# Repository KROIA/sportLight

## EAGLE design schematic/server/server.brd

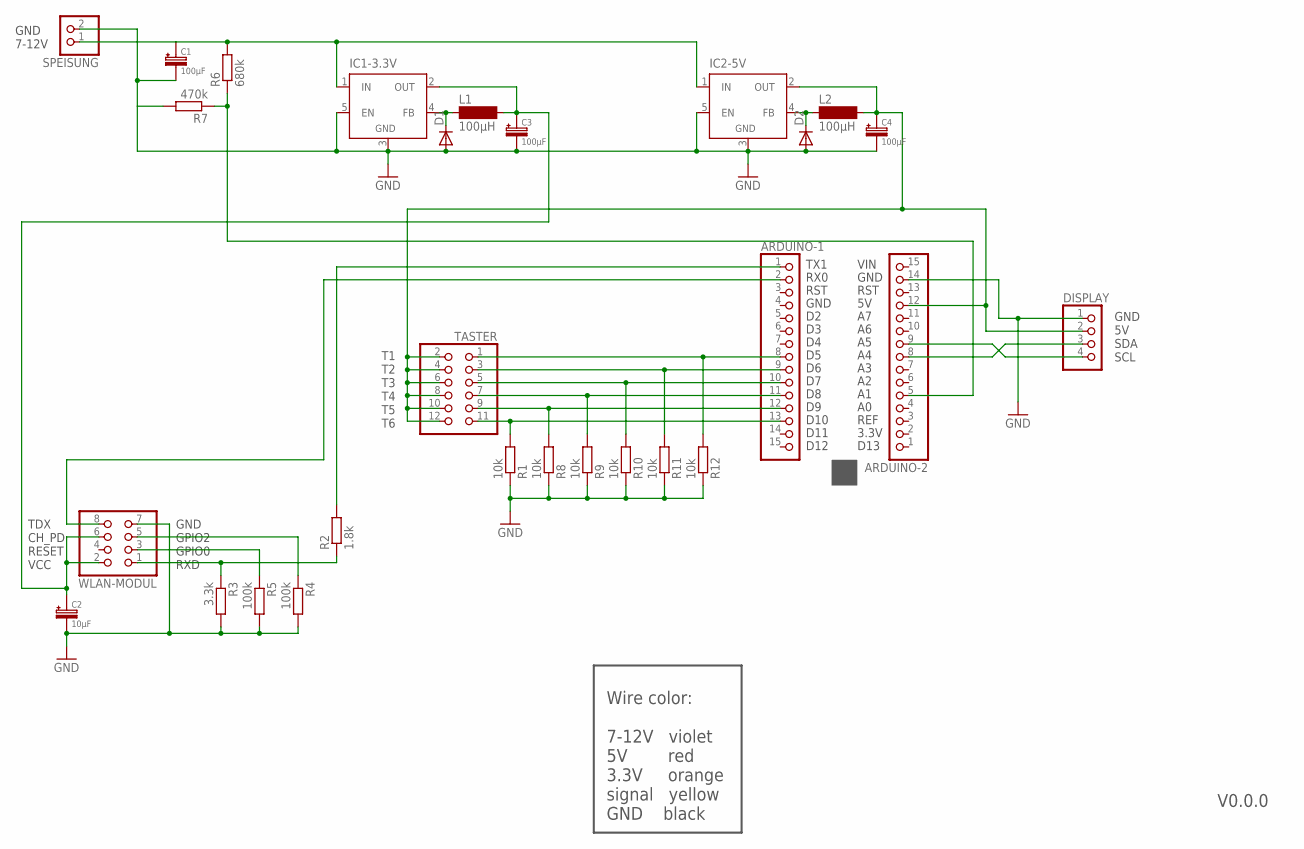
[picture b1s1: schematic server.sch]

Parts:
ARDUINO-1, ARDUINO-2: PINHD-1X15; 1X15
C1, C3, C4: 100µF; KONDENSATOR_ELEKTROLYT
C2: 10µF; KONDENSATOR_ELEKTROLYT
D1, D2: DIODE-D-2.5; D-2.5
DISPLAY: PINHD-1X4; 1X04
IC1-3.3V, IC2-5V: LM2596TV; TO220-51
L1, L2: 100µH; SM-L15A
R1: 10k; 0207/15
R2: 1.8k; 0207/10
R3: 3.3k; 0207/10
R4, R5: 100k; 0207/10
R6: 680k; 0204V
R7: 470k; 0204V
R8: 10k; 0207/12
R9: 10k; 0207/10
R10: 10k; 0207/7
R11: 10k; 0207/5V
R12: 10k; 0207/2V
SPEISUNG: PINHD-1X2; 1X02
TASTER: PINHD-2X6; 2X06
WLAN-MODUL: PINHD-2X4; 2X04

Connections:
GND: ARDUINO-2.14, C1.P$1, C2.P$1, C3.P$1, C4.P$1, D1.A, D2.A, DISPLAY.1, IC1-3.3V.3 (GND), IC1-3.3V.5 (EN), IC2-5V.3 (GND), IC2-5V.5 (EN), R1.1, R3.2, R4.2, R5.2, R7.2, R8.1, R9.1, R10.1, R11.1, R12.1, SPEISUNG.2, WLAN-MODUL.7
unnamed: D1.C, IC1-3.3V.4 (FB), L1.1
unnamed: ARDUINO-1.9, R11.2, TASTER.3
unnamed: C1.P$2, IC1-3.3V.1 (IN), IC2-5V.1 (IN), R6.2, SPEISUNG.1
unnamed: C2.P$2, C3.P$2, IC1-3.3V.2 (OUT), L1.2, WLAN-MODUL.2, WLAN-MODUL.6
unnamed: D2.C, IC2-5V.4 (FB), L2.1
unnamed: ARDUINO-1.13, R1.2, TASTER.11
unnamed: ARDUINO-2.5, R6.1, R7.1
unnamed: ARDUINO-2.8, DISPLAY.3
unnamed: ARDUINO-1.12, R8.2, TASTER.9
unnamed: ARDUINO-2.9, DISPLAY.4
unnamed: R2.1, R3.1, WLAN-MODUL.1
unnamed: R5.1, WLAN-MODUL.3
unnamed: R4.1, WLAN-MODUL.5
unnamed: ARDUINO-1.1, R2.2
unnamed: ARDUINO-1.2, WLAN-MODUL.8
unnamed: ARDUINO-1.11, R9.2, TASTER.7
unnamed: ARDUINO-1.10, R10.2, TASTER.5
unnamed: ARDUINO-2.12, C4.P$2, DISPLAY.2, IC2-5V.2 (OUT), L2.2, TASTER.2, TASTER.4, TASTER.6, TASTER.8, TASTER.10, TASTER.12
unnamed: ARDUINO-1.8, R12.2, TASTER.1

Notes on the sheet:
TX1 RX0 RST GND D2 D3 D4 D5 D6 D7 D8 D9 D10 D11 D12
GND GPIO2 GPIO0 RXD
TDX CH_PD RESET VCC
GND 7-12V
GND 5V SDA SCL
VIN GND RST 5V A7 A6 A5 A4 A3 A2 A1 A0 REF 3.3V D13
V0.0.0
T1 T2 T3 T4 T5 T6
Wire color: 7-12V violet 5V red 3.3V orange signal yellow GND black

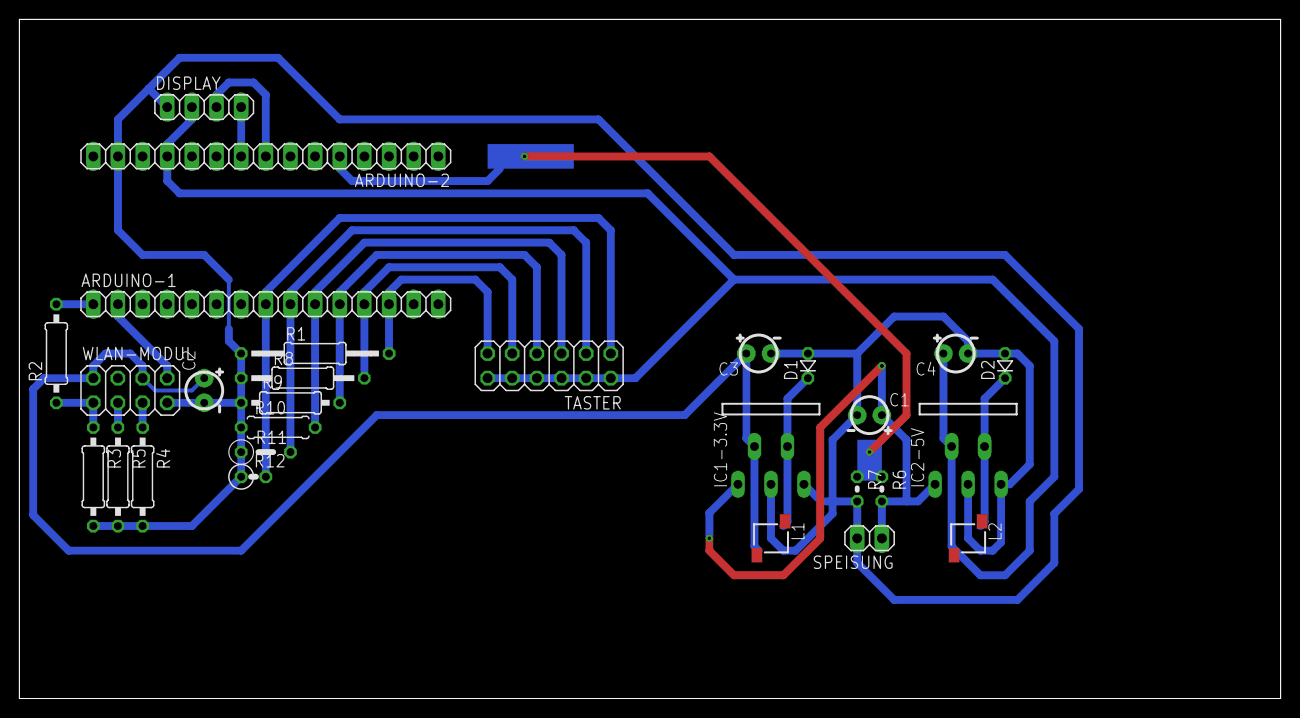
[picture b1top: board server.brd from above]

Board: 2 copper layers, 130.0 x 70.0 mm, 28 parts (0 on the bottom side), 20 nets.

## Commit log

2018-06-20 + sportlight
2018-06-26 v0.2.0
    Adding:
    voltage sensor
    MPU6050 calibrate
2018-06-28 + RGB_mode
2018-06-28 + serialCommand
    data|voltage|time
2018-06-28 voltageDisplayAnimationChange
2018-06-29 + server schematic
2018-06-29 + commands
2018-07-06 + server board
2018-07-10 pinoutChange
2018-07-11 + voltageDisplay
2018-07-11 + Mode
    + Menue_Info
    + Menue_Modus
2018-07-14 + mqtt
2018-07-19 bugfix
2018-08-14 +
    + Box[x] voltage in menue/info
    + testmodie
2018-09-11 communication done
    communication and clean up
